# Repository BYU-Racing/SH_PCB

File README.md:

Based on the BYU Racing Atlas board

Contributers:

Josh Wittwer

Josh Mix

### Description
STM32-powered data collector with hookups for analog and digital sensor signals and CAN connections. Interfacing with MCU is possible by USB or STLINK. Also includes headers for stacking a BMI IMU breakout board, an on-board thermistor, and a 12V SOC circuit.

### IO
https://byu.app.box.com/file/2516995544704 

### Connectors
#### Connector 1: (Molex 6-pin)
* CAN2_H
* CAN2_L
* REAR_SENSOR_12V
* REAR_SENSOR_5V
* IMU_CAN_H
* IMU_CAN_L
#### Connector 2: (Molex 6-pin)
* REAR_SENSOR_GND
* COOL_TMP_1_SIG
* COOL_TMP_2_SIG
* RIDE_H_SIG
* BRAKE_TMP_RR_SIG
* BRAKE_TMP_RL_SIG
#### Connector 3: (Molex 6-pin)
* FRONT_SENSOR_GND
* WHEEL_SPEED_R_SIG
* WHEEL_SPEED_L_SIG
* BRAKE_TMP_FL_SIG
* BRAKE_TMP_FR_SIG
* STEER_ANGLE_SIG
#### Connector 4: (Molex 6-pin)
* 12V
* GND
* FRONT_SENSOR_5V
* TOGG_3V3
* TOGG_1
* TOGG_2
#### Connector 5: (2x4 header, for testing only)
* BABY_SENSOR_5V
* BABY_SENSOR_GND
* COOL_PRES_SIG
* COOL_FLOW_SIG
* SUS_RR_SIG
* SUS_RL_SIG
* SUS_FL_SIG
* SIS_FR_SIG
#### Connector 6: USB
#### Connector 7: STLINK (1x6 header pin)
#### Connector 8: IMU (1x7 header socket)

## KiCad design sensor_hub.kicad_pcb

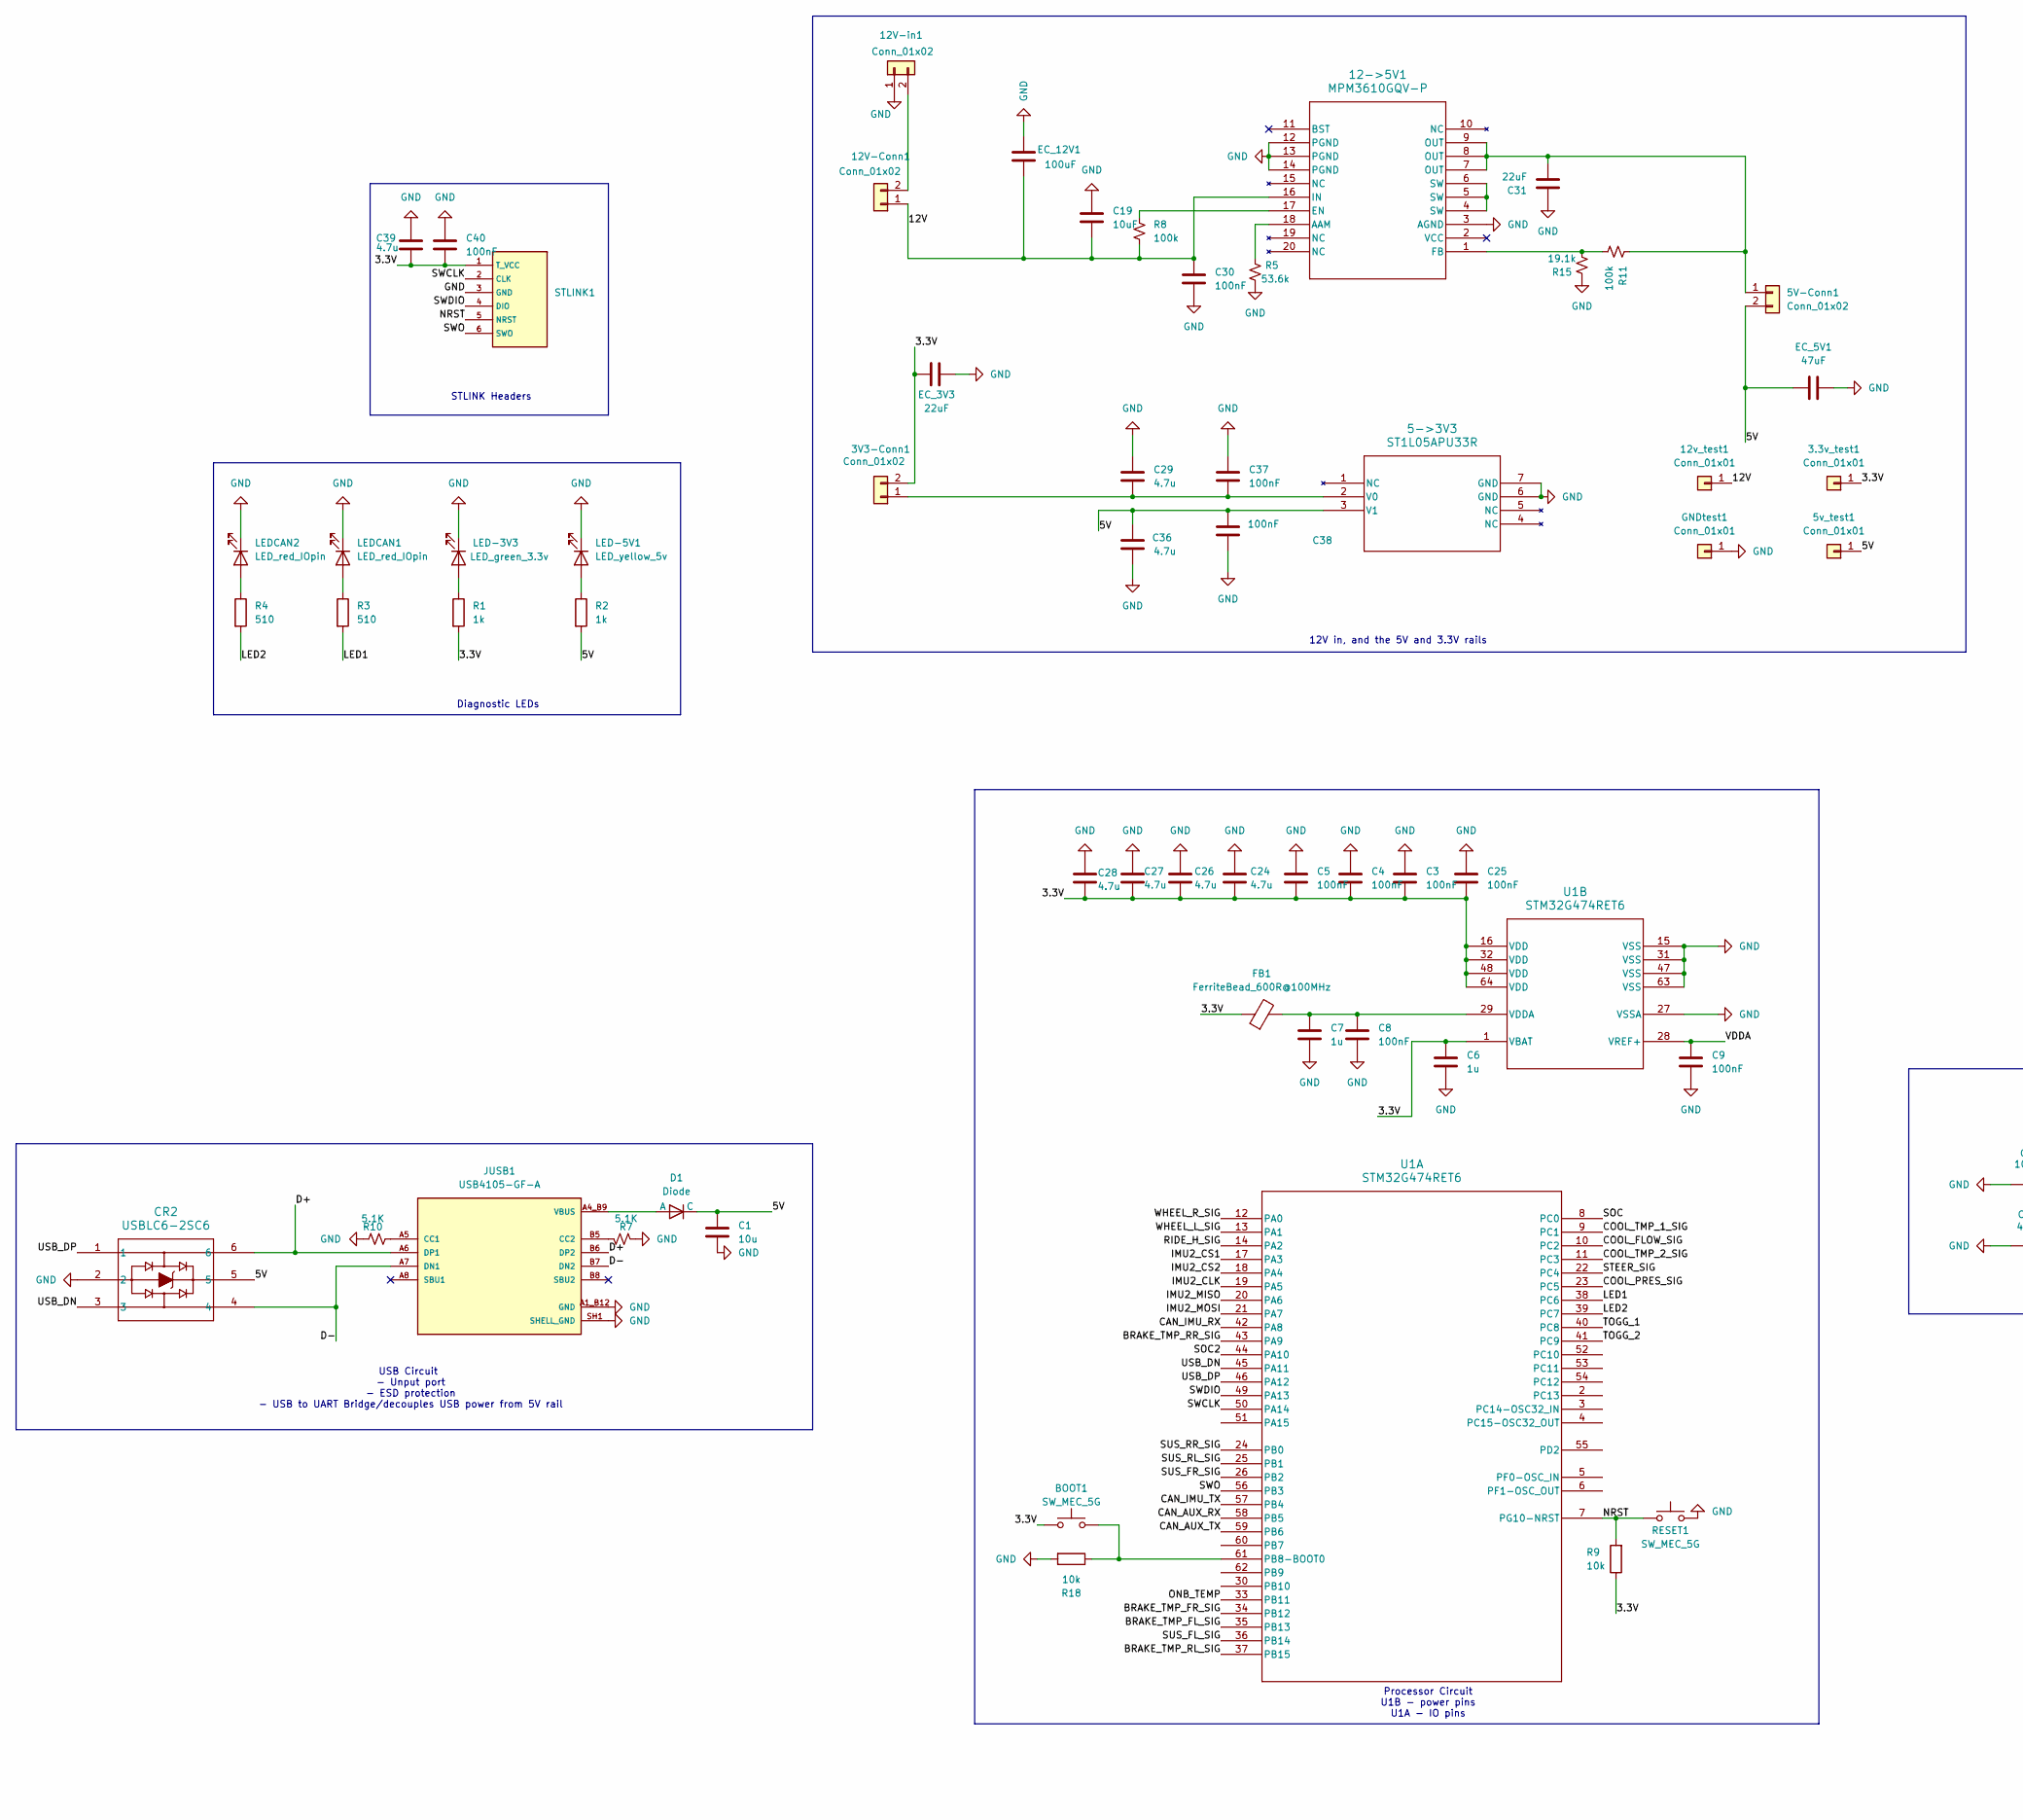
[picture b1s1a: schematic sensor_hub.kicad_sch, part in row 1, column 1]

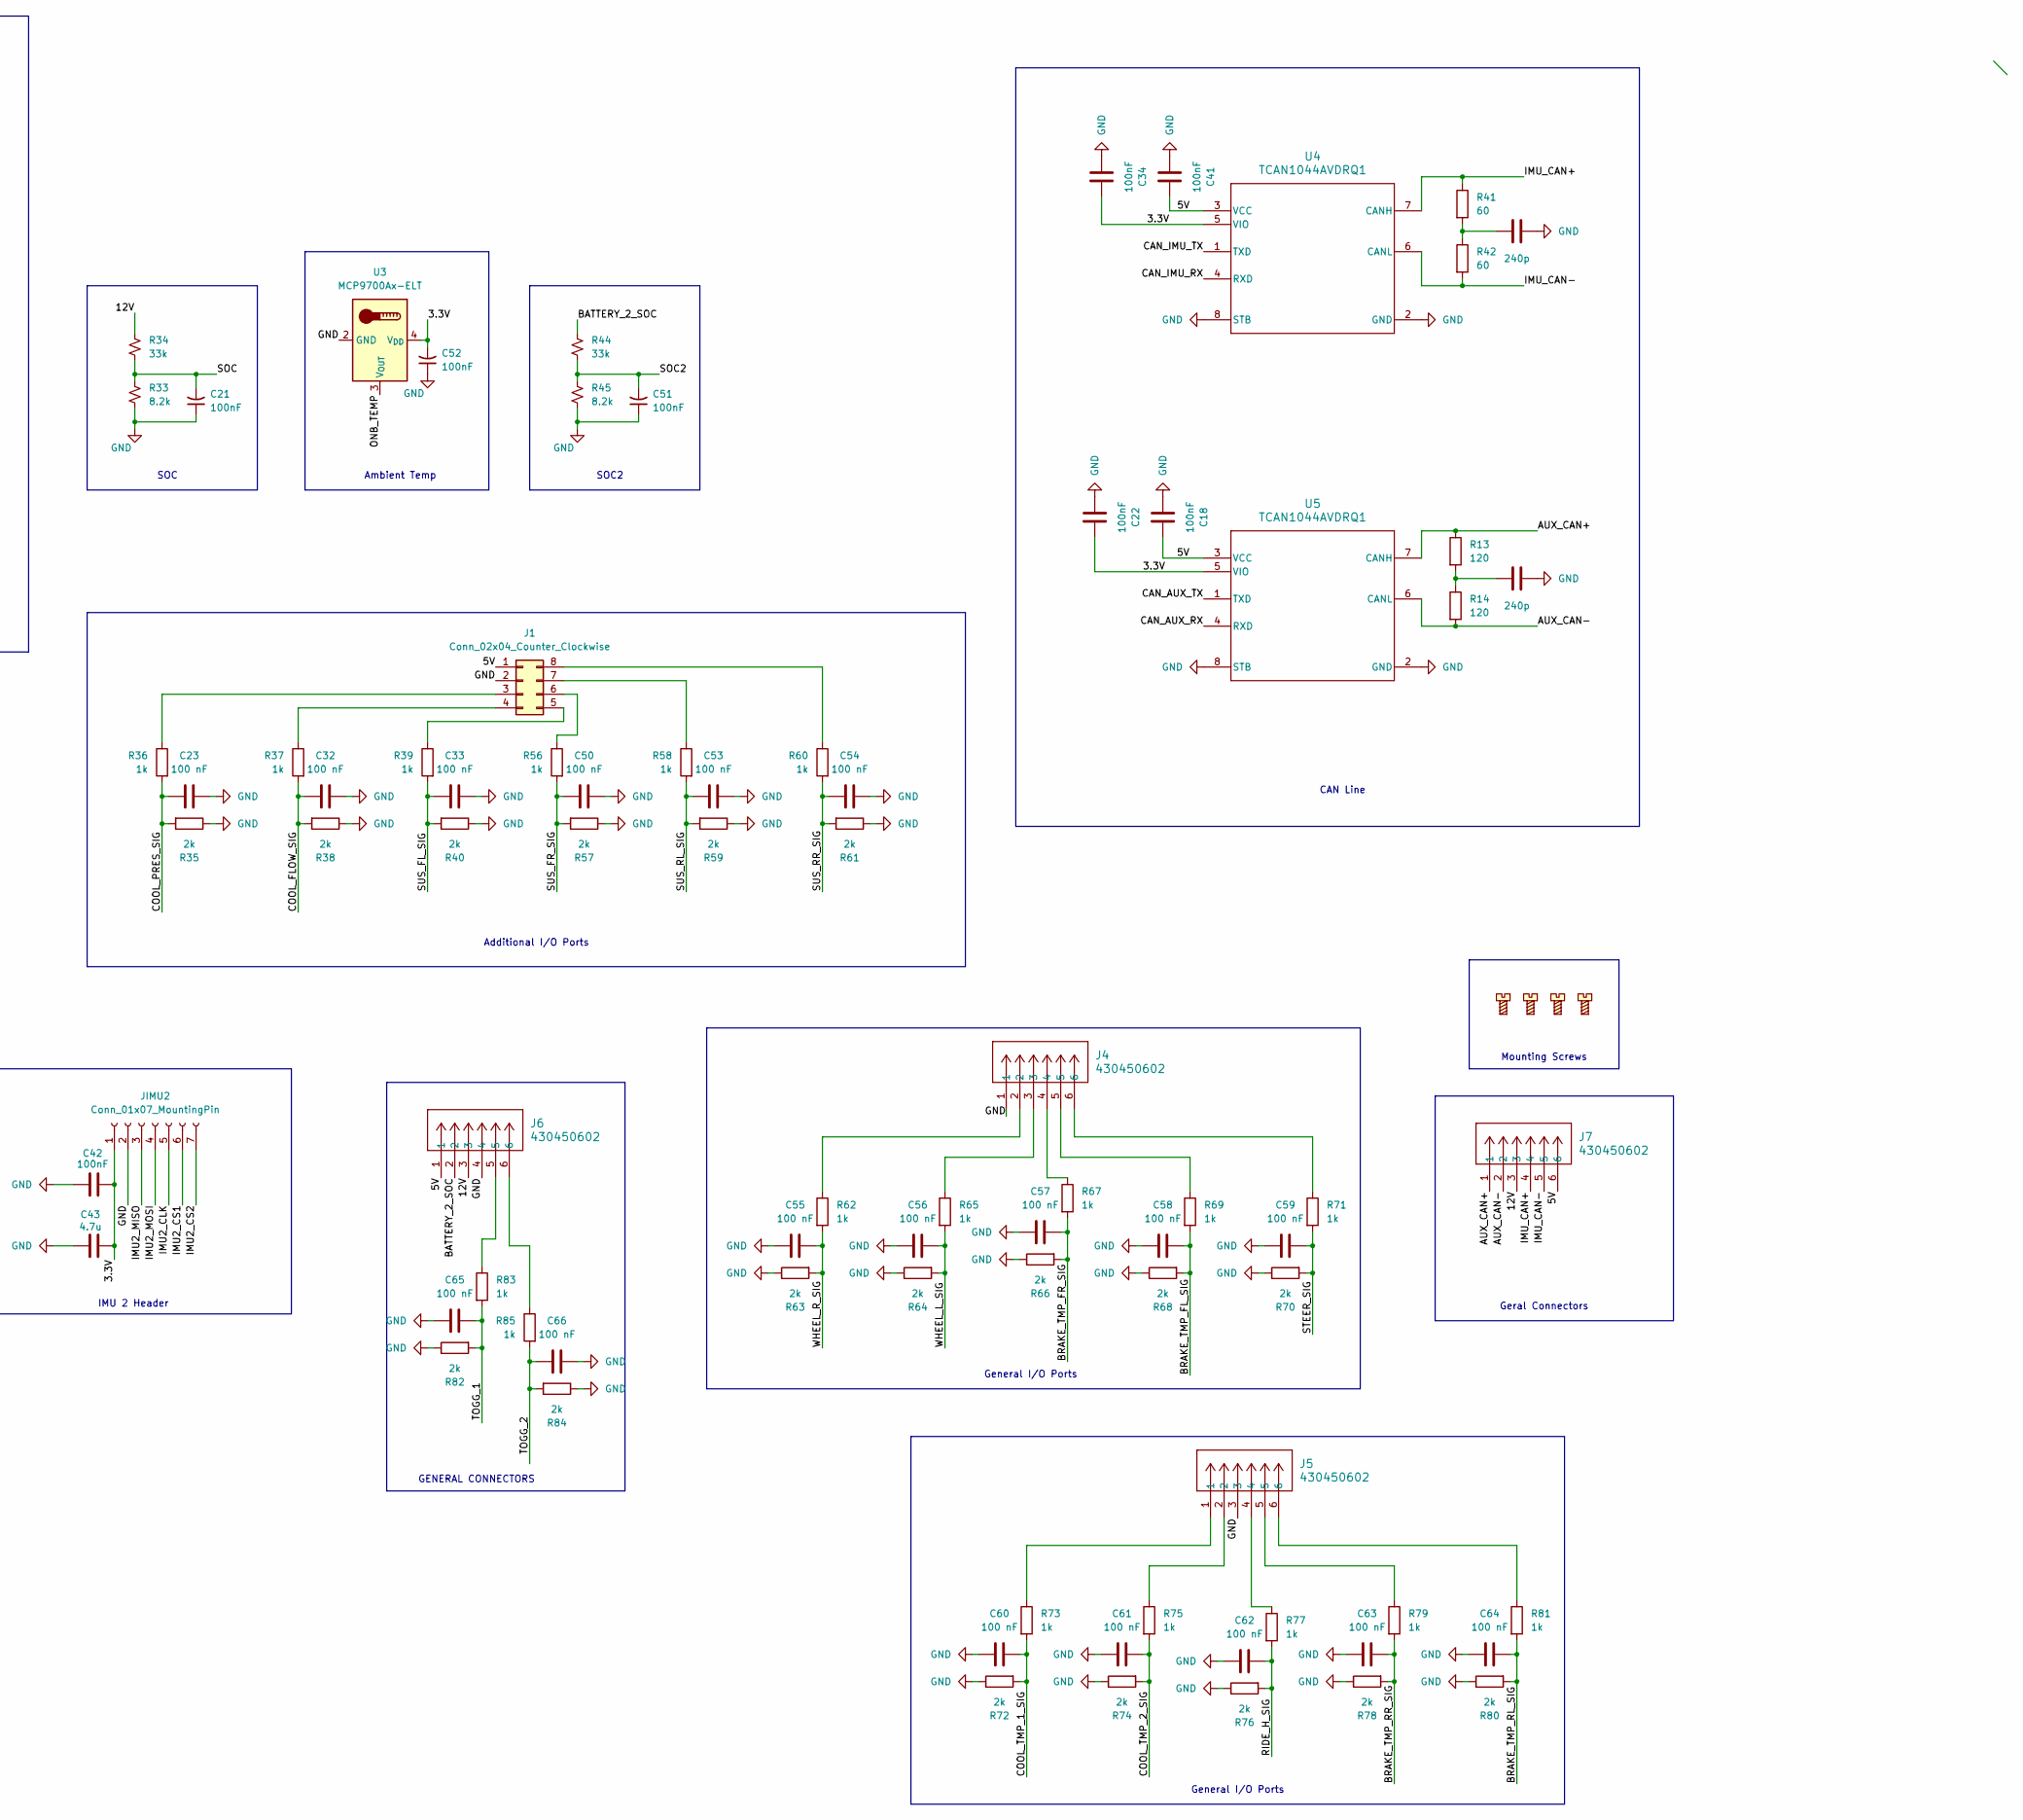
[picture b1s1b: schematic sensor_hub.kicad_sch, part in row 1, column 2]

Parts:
3.3v_test1, 5v_test1, 12v_test1: Conn_01x01; PinHeader_1x01_P2.54mm_Vertical
3V3-Conn1, 5V-Conn1, 12V-Conn1, 12V-in1: Conn_01x02; PinHeader_1x02_P2.54mm_Vertical
5->3V3: ST1L05APU33R; DFN_5APU33R_STM
12->5V1: MPM3610GQV-P
BOOT1: SW_MEC_5G; SW4_1825910-B_TEC
C1: 10u; C_0805_2012Metric_Pad1.18x1.45mm_HandSolder
C3, C4, C5, C8, C9, C18, C21, C22, C25, C30, C34, C37, C38, C40, C41, C42, C51, C52: 100nF; C_0805_2012Metric_Pad1.18x1.45mm_HandSolder
C6, C7: 1u; C_0805_2012Metric_Pad1.18x1.45mm_HandSolder
C15, C35: 240p; C_0805_2012Metric_Pad1.18x1.45mm_HandSolder
C19: 10uF; C_0805_2012Metric_Pad1.18x1.45mm_HandSolder
C23, C32, C33, C50, C53, C54, C55, C56, C57, C58, C59, C60, C61, C62, C63, C64, C65, C66: 100 nF; C_0805_2012Metric_Pad1.18x1.45mm_HandSolder
C24, C26, C27, C28, C29, C36, C39, C43: 4.7u; C_0805_2012Metric_Pad1.18x1.45mm_HandSolder
C31: 22uF; C_0805_2012Metric_Pad1.18x1.45mm_HandSolder
CR2: USBLC6-2SC6; SOT23-6L_STM
D1: Diode; P35_SOD-123F
EC_3V3: 22uF; CP_Radial_D7.5mm_P2.50mm
EC_5V1: 47uF; CP_Radial_D7.5mm_P2.50mm
EC_12V1: 100uF; CP_Radial_D7.5mm_P2.50mm
FB1: FerriteBead_600R@100MHz; GZ1608D601TF
GNDtest1: Conn_01x01; PinHeader_1x01_P2.54mm_Vertical
H1, H2, H3, H4: Mounting_Screw; MountingHole_3.2mm_M3_DIN965
J1: Conn_02x04_Counter_Clockwise; PinHeader_2x04_P2.54mm_Vertical
J4, J5, J6, J7: 430450602; CONN_SD-43045-001_06_MOL
JIMU2: Conn_01x07_MountingPin; PinHeader_1x07_P2.00mm_Vertical
JUSB1: USB4105-GF-A; GCT_USB4105-GF-A; PARTREV B4
LED-3V3: LED_green_3.3v; LED_0805_2012Metric
LED-5V1: LED_yellow_5v; LED_0805_2012Metric
LEDCAN1, LEDCAN2: LED_red_IOpin; LED_0805_2012Metric
R1, R2, R36, R37, R39, R56, R58, R60, R62, R65, R67, R69, R71, R73, R75, R77, R79, R81, R83, R85: 1k; R_0805_2012Metric_Pad1.20x1.40mm_HandSolder
R3, R4: 510; R_0805_2012Metric_Pad1.20x1.40mm_HandSolder
R5: 53.6k; R_0805_2012Metric_Pad1.20x1.40mm_HandSolder
R7, R10: 5.1K; R_0805_2012Metric_Pad1.20x1.40mm_HandSolder
R8, R11: 100k; R_0805_2012Metric_Pad1.20x1.40mm_HandSolder
R9, R18: 10k; R_0805_2012Metric_Pad1.20x1.40mm_HandSolder
R13, R14: 120; R_0805_2012Metric_Pad1.20x1.40mm_HandSolder
R15: 19.1k; R_0805_2012Metric_Pad1.20x1.40mm_HandSolder
R33, R45: 8.2k; R_0805_2012Metric_Pad1.20x1.40mm_HandSolder
R34, R44: 33k; R_0805_2012Metric_Pad1.20x1.40mm_HandSolder
R35, R38, R40, R57, R59, R61, R63, R64, R66, R68, R70, R72, R74, R76, R78, R80, R82, R84: 2k; R_0805_2012Metric_Pad1.20x1.40mm_HandSolder
R41, R42: 60; R_0805_2012Metric_Pad1.20x1.40mm_HandSolder
RESET1: SW_MEC_5G; SW4_1825910-B_TEC
STLINK1: PinHeader_1x06_P2.54mm_Vertical
U1: STM32G474RET6; STM32G474RE
U3: MCP9700Ax-ELT; SOT-353_SC-70-5
U4, U5: TCAN1044AVDRQ1; TSOT-23-8_HandSoldering

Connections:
/3.3V: 3.3v_test1.1, 3V3-Conn1.2, BOOT1.3 (B), BOOT1.4 (B), C3.2, C4.2, C5.2, C6.1, C22.2, C24.2, C25.2, C26.2, C27.2, C28.2, C34.2, C39.2, C40.2, C42.2, C43.2, C52.2, EC_3V3.1, FB1.1, JIMU2.1, R1.2, R9.1, STLINK1.1 (T_VCC), U1.1 (VBAT), U1.16 (VDD), U1.32 (VDD), U1.48 (VDD), U1.64 (VDD), U3.4 (V_{DD}), U4.5 (VIO), U5.5 (VIO); also elsewhere on the board
/5V: 5->3V3.3 (V1), 5V-Conn1.2, 5v_test1.1 (Pin_1_1), C1.1, C18.2, C36.1, C38.2, C41.2, CR2.5, D1.2 (C), EC_5V1.1, J1.1, J6.1, J7.6, R2.2, U4.3 (VCC), U5.3 (VCC)
/12V: 12->5V1.16 (IN), 12V-Conn1.1, 12v_test1.1 (Pin_1_1), C19.2, C30.1, EC_12V1.1, J6.3, J7.3, R8.2, R34.1
/AUX_CAN+: J7.1, R13.1, U5.7 (CANH)
/AUX_CAN-: J7.2, R14.2, U5.6 (CANL)
/BATTERY_2_SOC: J6.2, R44.1
/BRAKE_TMP_FL_SIG: C58.2, R68.2, R69.2, U1.35 (PB13)
/BRAKE_TMP_FR_SIG: C57.2, R66.2, R67.2, U1.34 (PB12)
/BRAKE_TMP_RL_SIG: C64.2, R80.2, R81.2, U1.37 (PB15)
/BRAKE_TMP_RR_SIG: C63.2, R78.2, R79.2, U1.43 (PA9)
/CAN_AUX_RX: U1.58 (PB5), U5.4 (RXD)
/CAN_AUX_TX: U1.59 (PB6), U5.1 (TXD)
/CAN_IMU_RX: U1.42 (PA8), U4.4 (RXD)
/CAN_IMU_TX: U1.57 (PB4), U4.1 (TXD)
/COOL_FLOW_SIG: C32.2, R37.2, R38.2, U1.10 (PC2)
/COOL_PRES_SIG: C23.2, R35.2, R36.2, U1.23 (PC5)
/COOL_TMP_1_SIG: C60.2, R72.2, R73.2, U1.9 (PC1)
/COOL_TMP_2_SIG: C61.2, R74.2, R75.2, U1.11 (PC3)
/D+: CR2.6, JUSB1.A6 (DP1), JUSB1.B6 (DP2)
/D-: CR2.4, JUSB1.A7 (DN1), JUSB1.B7 (DN2)
/IMU2_CLK: JIMU2.5, U1.19 (PA5); also elsewhere on the board
/IMU2_CS1: JIMU2.6, U1.17 (PA3); also elsewhere on the board
/IMU2_CS2: JIMU2.7, U1.18 (PA4); also elsewhere on the board
/IMU2_MISO: JIMU2.3, U1.20 (PA6); also elsewhere on the board
/IMU2_MOSI: JIMU2.4, U1.21 (PA7); also elsewhere on the board
/IMU_CAN+: J7.4, R41.1, U4.7 (CANH)
/IMU_CAN-: J7.5, R42.2, U4.6 (CANL)
/LED1: R3.2, U1.38 (PC6)
/LED2: R4.2, U1.39 (PC7)
/NRST: R9.2, RESET1.1 (A), RESET1.2 (A), STLINK1.5 (NRST), U1.7 (PG10-NRST)
/ONB_TEMP: U1.33 (PB11), U3.3 (V_{OUT})
/RIDE_H_SIG: C62.2, R76.2, R77.2, U1.14 (PA2)
/SOC: C21.2, R33.1, R34.2, U1.8 (PC0)
/SOC2: C51.2, R44.2, R45.1, U1.44 (PA10)
/STEER_SIG: C59.2, R70.2, R71.2, U1.22 (PC4)
/SUS_FL_SIG: C33.2, R39.2, R40.2, U1.36 (PB14)
/SUS_FR_SIG: C50.2, R56.2, R57.2, U1.26 (PB2)
/SUS_RL_SIG: C53.2, R58.2, R59.2, U1.25 (PB1)
/SUS_RR_SIG: C54.2, R60.2, R61.2, U1.24 (PB0)
/SWCLK: STLINK1.2 (CLK), U1.50 (PA14)
/SWDIO: STLINK1.4 (DIO), U1.49 (PA13)
/SWO: STLINK1.6 (SWO), U1.56 (PB3)
/TOGG_1: C65.2, R82.2, R83.2, U1.40 (PC8)
/TOGG_2: C66.2, R84.2, R85.2, U1.41 (PC9)
/USB_DN: CR2.3, U1.45 (PA11)
/USB_DP: CR2.1, U1.46 (PA12)
/VDDA: C9.1, U1.28 (VREF+)
/WHEEL_L_SIG: C56.2, R64.2, R65.2, U1.13 (PA1)
/WHEEL_R_SIG: C55.2, R62.2, R63.2, U1.12 (PA0)
GND: 5->3V3.6 (GND), 5->3V3.7 (GND), 12->5V1.3 (AGND), 12->5V1.12 (PGND), 12->5V1.13 (PGND), 12->5V1.14 (PGND), 12V-in1.1, C1.2, C3.1, C4.1, C5.1, C6.2, C7.2, C8.2, C9.2, C15.1, C18.1, C19.1, C21.1, C22.1, C23.1, C24.1, C25.1, C26.1, C27.1, C28.1, C29.1, C30.2, C31.1, C32.1, C33.1, C34.1, C35.1, C36.2, C37.1, C38.1, C39.1, C40.1, C41.1, C42.1, C43.1, C50.1, C51.1, C52.1, C53.1, C54.1, C55.1, C56.1, C57.1, C58.1, C59.1, C60.1, C61.1, C62.1, C63.1, C64.1, C65.1, C66.1, CR2.2, EC_3V3.2, EC_5V1.2, EC_12V1.2, GNDtest1.1, J1.2, J4.1, J5.3, J6.4, JIMU2.2, JUSB1.A1_B12 (GND), JUSB1.B1_A12 (GND), JUSB1.SH1 (SHELL_GND), JUSB1.SH2 (SHELL_GND), JUSB1.SH3 (SHELL_GND), JUSB1.SH4 (SHELL_GND), LED-3V3.1 (K), LED-5V1.1 (K), LEDCAN1.1 (K), LEDCAN2.1 (K), R5.2, R7.2, R10.2, R15.1, R18.2, R33.2, R35.1, R38.1, R40.1, R45.2, R57.1, R59.1, R61.1, R63.1, R64.1, R66.1, R68.1, R70.1, R72.1, R74.1, R76.1, R78.1, R80.1, R82.1, R84.1, RESET1.3 (B), RESET1.4 (B), STLINK1.3 (GND), U1.15 (VSS), U1.27 (VSSA), U1.31 (VSS), U1.47 (VSS), U1.63 (VSS), U3.2 (GND), U4.2 (GND), U4.8 (STB), U5.2 (GND), U5.8 (STB); also elsewhere on the board
unnamed: 3V3-Conn1.1, 5->3V3.2 (V0), C29.2, C37.2
unnamed: 5V-Conn1.1, 12->5V1.7 (OUT), 12->5V1.8 (OUT), 12->5V1.9 (OUT), C31.2, R11.1
unnamed: 12->5V1.18 (AAM), R5.1
unnamed: 12->5V1.17 (EN), R8.1
unnamed: 12->5V1.1 (FB), R11.2, R15.2
unnamed: 12->5V1.4 (SW), 12->5V1.5 (SW), 12->5V1.6 (SW)
unnamed: 12V-Conn1.2, 12V-in1.2
unnamed: C15.2, R13.2, R14.1
unnamed: C35.2, R41.2, R42.1
unnamed: J1.3, R36.1
unnamed: J1.4, R37.1
unnamed: J1.5, R39.1
unnamed: J1.6, R56.1
unnamed: J1.7, R58.1
unnamed: J1.8, R60.1
unnamed: J4.2, R62.1
unnamed: J4.3, R65.1
unnamed: J4.4, R67.1
unnamed: J4.5, R69.1
unnamed: J4.6, R71.1
unnamed: J5.1, R73.1
unnamed: J5.2, R75.1
unnamed: J5.4, R77.1
unnamed: J5.5, R79.1
unnamed: J5.6, R81.1
unnamed: J6.5, R83.1
unnamed: J6.6, R85.1
unnamed: JUSB1.A5 (CC1), R10.1
unnamed: JUSB1.B5 (CC2), R7.1
unnamed: LED-3V3.2 (A), R1.1
unnamed: LED-5V1.2 (A), R2.1
unnamed: LEDCAN1.2 (A), R3.1
unnamed: LEDCAN2.2 (A), R4.1
unnamed: BOOT1.1 (A), BOOT1.2 (A), R18.1, U1.61 (PB8-BOOT0)
unnamed: C7.1, C8.1, FB1.2, U1.29 (VDDA)
VBUS: D1.1 (A), JUSB1.A4_B9 (VBUS), JUSB1.B4_A9 (VBUS)

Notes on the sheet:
General I/O Ports
USB Circuit - Unput port - ESD protection - USB to UART Bridge/decouples USB power from 5V rail
SOC2
Mounting Screws
Ambient Temp
SOC
STLINK Headers
GENERAL CONNECTORS
IMU 2 Header
12V in, and the 5V and 3.3V rails
Additional I/O Ports
Geral Connectors
Processor Circuit U1B - power pins U1A - IO pins
CAN Line
Diagnostic LEDs

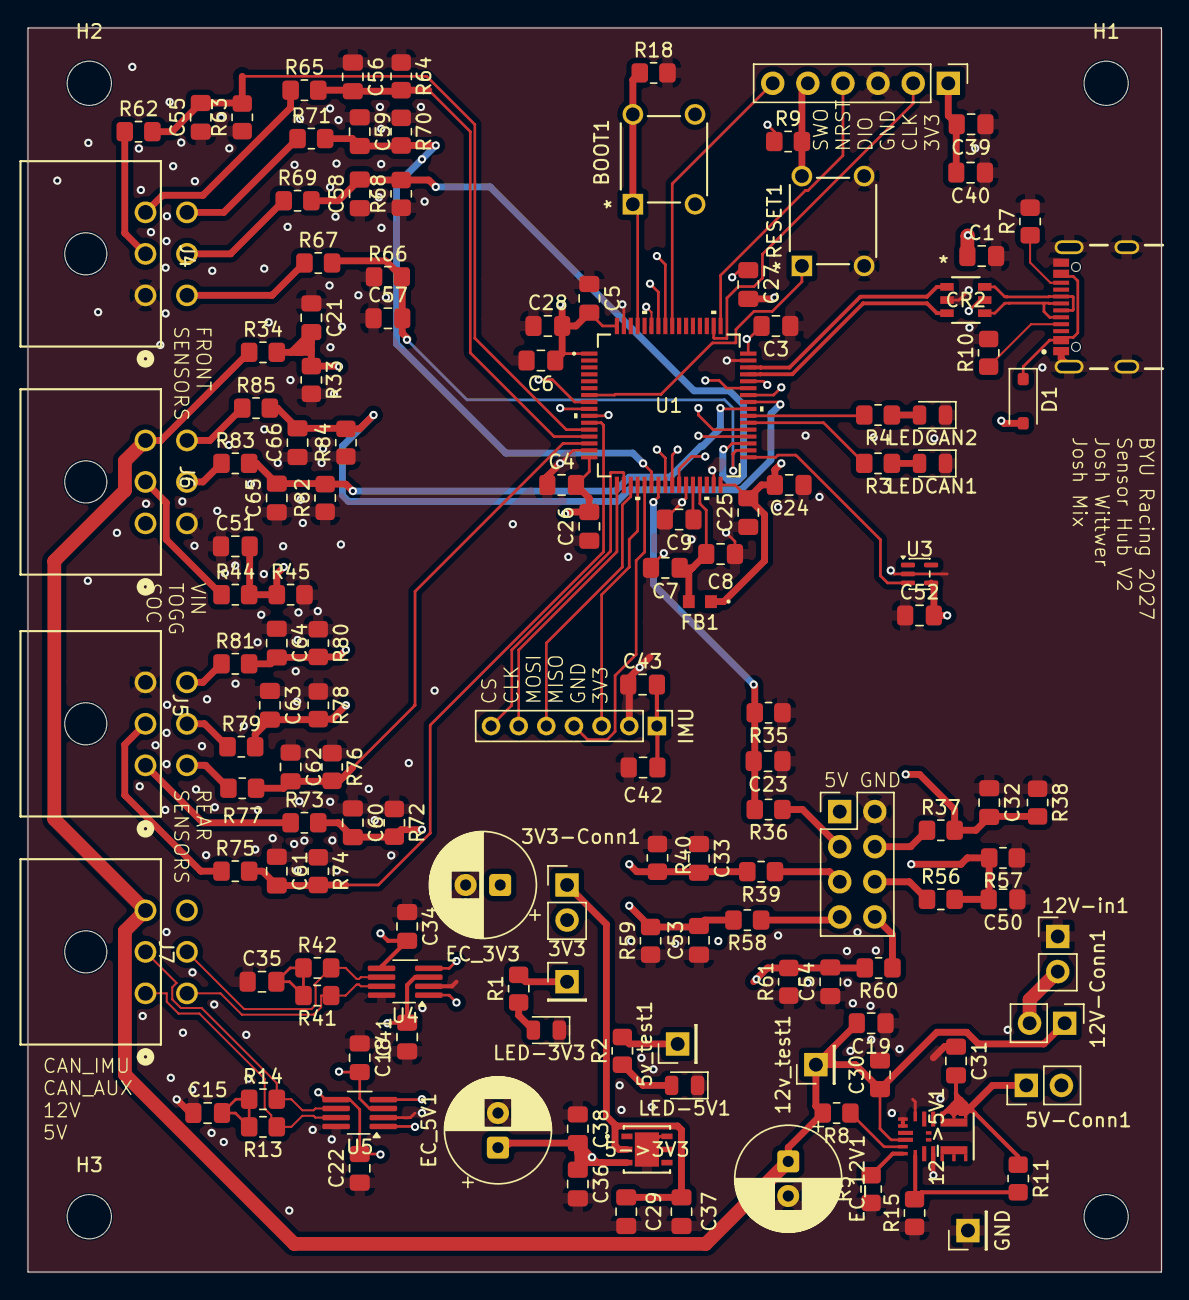
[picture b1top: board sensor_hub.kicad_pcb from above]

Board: 4 copper layers, 82.0 x 90.0 mm, 145 parts (0 on the bottom side), 86 nets.

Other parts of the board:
3V3: Conn_01x01; PinHeader_1x01_P2.54mm_Vertical
GND: Conn_01x01; PinHeader_1x01_P2.54mm_Vertical
IMU: Conn_01x07_MountingPin; PinHeader_1x07_P2.00mm_Vertical

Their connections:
/3.3V: 3V3.1 (Pin_1_1), IMU.1; also elsewhere on the board
/IMU2_CLK: IMU.5; also elsewhere on the board
/IMU2_CS1: IMU.6; also elsewhere on the board
/IMU2_CS2: IMU.7; also elsewhere on the board
/IMU2_MISO: IMU.3; also elsewhere on the board
/IMU2_MOSI: IMU.4; also elsewhere on the board
GND: GND.1 (Pin_1_1), IMU.2; also elsewhere on the board
